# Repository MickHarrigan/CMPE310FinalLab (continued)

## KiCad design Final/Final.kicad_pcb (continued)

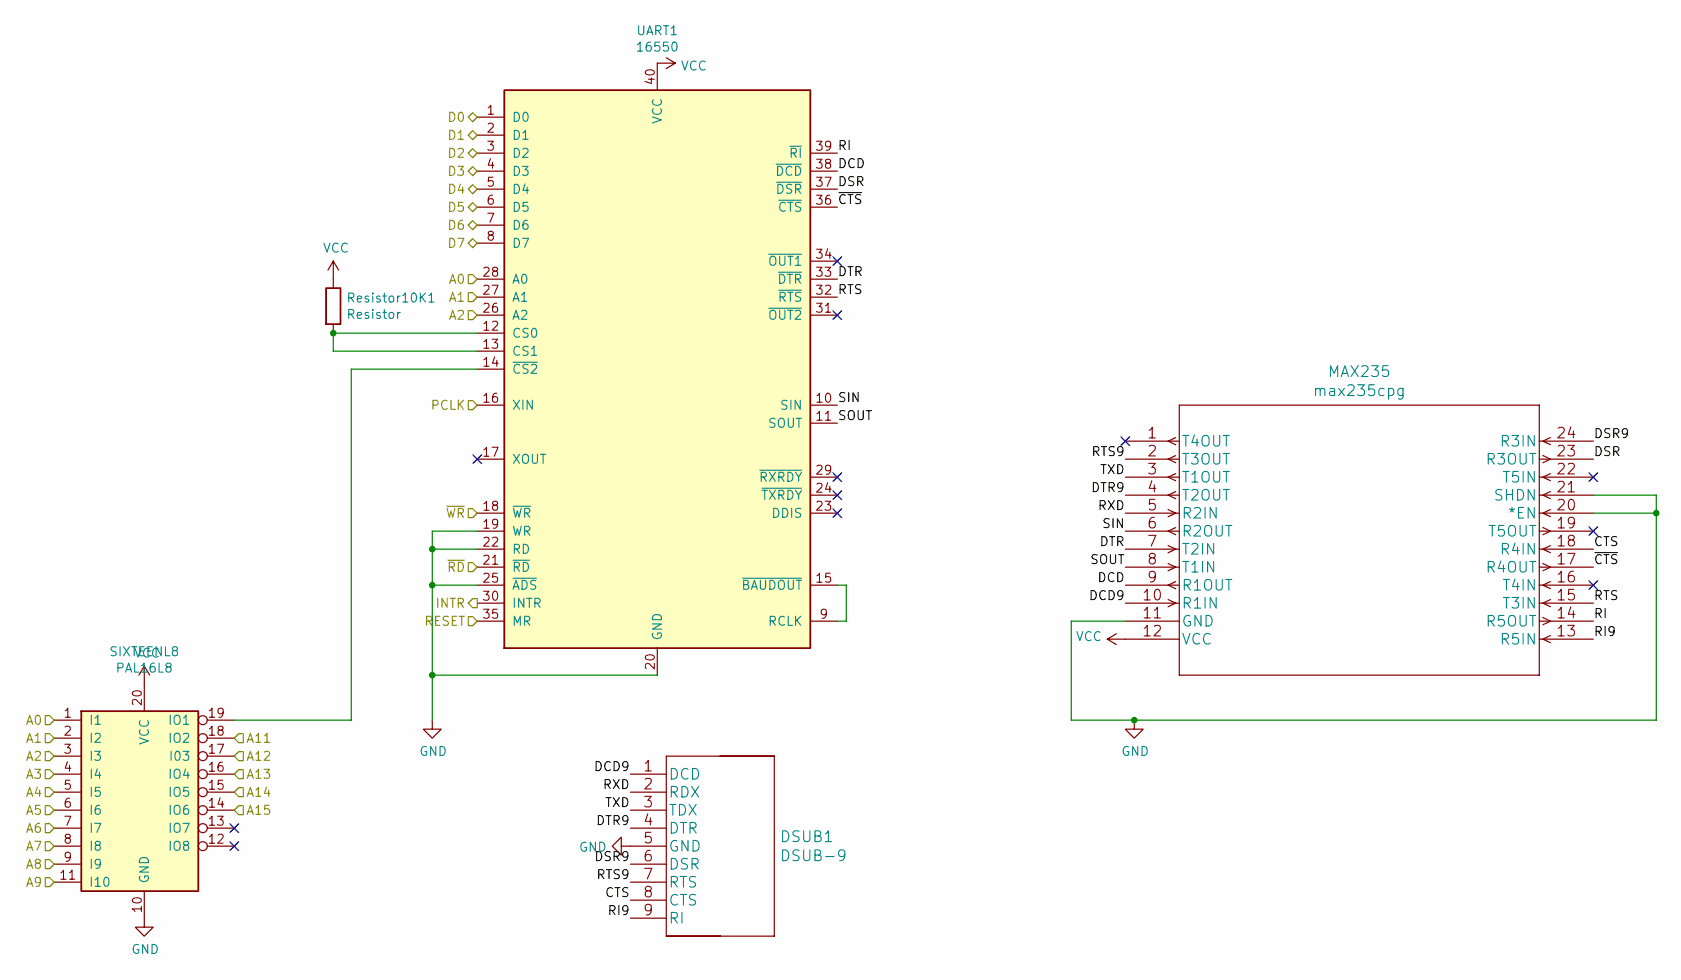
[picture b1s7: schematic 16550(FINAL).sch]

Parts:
DSUB1: DSUB-9
MAX235: max235cpg
Resistor10K1: Resistor
SIXTEENL8: PAL16L8
UART1: 16550; DIP-40_W15.24mm

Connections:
/16550/CTS: DSUB1.8 (CTS), MAX235.18 (R4IN)
/16550/DCD: MAX235.9 (R1OUT), UART1.38 (~DCD~)
/16550/DCD9: DSUB1.1 (DCD), MAX235.10 (R1IN)
/16550/DSR: MAX235.23 (R3OUT), UART1.37 (~DSR~)
/16550/DSR9: DSUB1.6 (DSR), MAX235.24 (R3IN)
/16550/DTR: MAX235.7 (T2IN), UART1.33 (~DTR~)
/16550/DTR9: DSUB1.4 (DTR), MAX235.4 (T2OUT)
/16550/RI: MAX235.14 (R5OUT), UART1.39 (~RI~)
/16550/RI9: DSUB1.9 (RI), MAX235.13 (R5IN)
/16550/RTS: MAX235.15 (T3IN), UART1.32 (~RTS~)
/16550/RTS9: DSUB1.7 (RTS), MAX235.2 (T3OUT)
/16550/RXD: DSUB1.2 (RDX), MAX235.5 (R2IN)
/16550/SIN: MAX235.6 (R2OUT), UART1.10 (SIN)
/16550/SOUT: MAX235.8 (T1IN), UART1.11 (SOUT)
/16550/TXD: DSUB1.3 (TDX), MAX235.3 (T1OUT)
/16550/~CTS: MAX235.17 (R4OUT), UART1.36 (~CTS~)
/16550_INTR: UART1.30 (INTR); also elsewhere on the board
/A0: SIXTEENL8.1 (I1), UART1.28 (A0); also elsewhere on the board
/A1: SIXTEENL8.2 (I2), UART1.27 (A1); also elsewhere on the board
/A2: SIXTEENL8.3 (I3), UART1.26 (A2); also elsewhere on the board
/A3: SIXTEENL8.4 (I4); also elsewhere on the board
/A4: SIXTEENL8.5 (I5); also elsewhere on the board
/A5: SIXTEENL8.6 (I6); also elsewhere on the board
/A6: SIXTEENL8.7 (I7); also elsewhere on the board
/A7: SIXTEENL8.8 (I8); also elsewhere on the board
/A8: SIXTEENL8.9 (I9); also elsewhere on the board
/A9: SIXTEENL8.11 (I10); also elsewhere on the board
/A11: SIXTEENL8.18 (IO2); also elsewhere on the board
/A12: SIXTEENL8.17 (I03); also elsewhere on the board
/A13: SIXTEENL8.16 (IO4); also elsewhere on the board
/A14: SIXTEENL8.15 (IO5); also elsewhere on the board
/A15: SIXTEENL8.14 (IO6); also elsewhere on the board
/D0: UART1.1 (D0); also elsewhere on the board
/D1: UART1.2 (D1); also elsewhere on the board
/D2: UART1.3 (D2); also elsewhere on the board
/D3: UART1.4 (D3); also elsewhere on the board
/D4: UART1.5 (D4); also elsewhere on the board
/D5: UART1.6 (D5); also elsewhere on the board
/D6: UART1.7 (D6); also elsewhere on the board
/D7: UART1.8 (D7); also elsewhere on the board
/PCLK: UART1.16 (XIN); also elsewhere on the board
/RESET: UART1.35 (MR); also elsewhere on the board
/~RD: UART1.21 (~RD~); also elsewhere on the board
/~WR: UART1.18 (~WR~); also elsewhere on the board
GND: DSUB1.5 (GND), MAX235.11 (GND), MAX235.20 (*EN), MAX235.21 (SHDN), SIXTEENL8.10 (GND), UART1.19 (WR), UART1.20 (GND), UART1.22 (RD), UART1.25 (~ADS~); also elsewhere on the board
unnamed: Resistor10K1.2, UART1.12 (CS0), UART1.13 (CS1)
unnamed: SIXTEENL8.19 (IO1), UART1.14 (~CS2~)
unnamed: UART1.9 (RCLK), UART1.15 (~BAUDOUT~)
VCC: MAX235.12 (VCC), Resistor10K1.1, SIXTEENL8.20 (VCC), UART1.40 (VCC); also elsewhere on the board

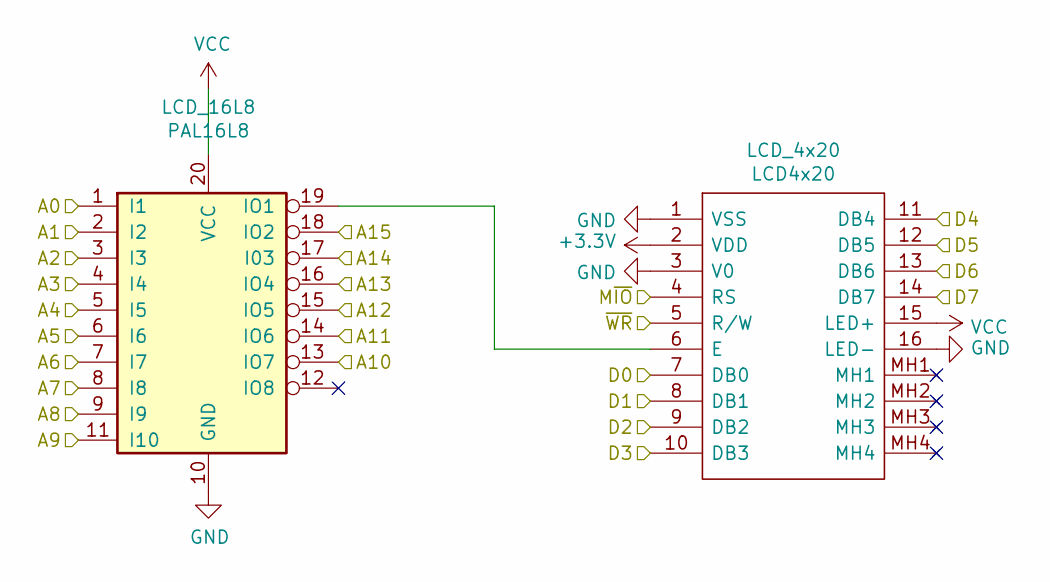
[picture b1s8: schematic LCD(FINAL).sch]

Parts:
LCD_4x20: LCD4x20; Mouser Part Number 763-0420AZFLYBW33V3
LCD_16L8: PAL16L8

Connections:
+3V3: LCD_4x20.2 (VDD)
/A0: LCD_16L8.1 (I1); also elsewhere on the board
/A1: LCD_16L8.2 (I2); also elsewhere on the board
/A2: LCD_16L8.3 (I3); also elsewhere on the board
/A3: LCD_16L8.4 (I4); also elsewhere on the board
/A4: LCD_16L8.5 (I5); also elsewhere on the board
/A5: LCD_16L8.6 (I6); also elsewhere on the board
/A6: LCD_16L8.7 (I7); also elsewhere on the board
/A7: LCD_16L8.8 (I8); also elsewhere on the board
/A8: LCD_16L8.9 (I9); also elsewhere on the board
/A9: LCD_16L8.11 (I10); also elsewhere on the board
/A10: LCD_16L8.13 (IO7); also elsewhere on the board
/A11: LCD_16L8.14 (IO6); also elsewhere on the board
/A12: LCD_16L8.15 (IO5); also elsewhere on the board
/A13: LCD_16L8.16 (IO4); also elsewhere on the board
/A14: LCD_16L8.17 (I03); also elsewhere on the board
/A15: LCD_16L8.18 (IO2); also elsewhere on the board
/D0: LCD_4x20.7 (DB0); also elsewhere on the board
/D1: LCD_4x20.8 (DB1); also elsewhere on the board
/D2: LCD_4x20.9 (DB2); also elsewhere on the board
/D3: LCD_4x20.10 (DB3); also elsewhere on the board
/D4: LCD_4x20.11 (DB4); also elsewhere on the board
/D5: LCD_4x20.12 (DB5); also elsewhere on the board
/D6: LCD_4x20.13 (DB6); also elsewhere on the board
/D7: LCD_4x20.14 (DB7); also elsewhere on the board
/M~IO: LCD_4x20.4 (RS); also elsewhere on the board
/~WR: LCD_4x20.5 (R/W); also elsewhere on the board
GND: LCD_4x20.1 (VSS), LCD_4x20.3 (V0), LCD_4x20.16 (LED-), LCD_16L8.10 (GND); also elsewhere on the board
unnamed: LCD_4x20.6 (E), LCD_16L8.19 (IO1)
VCC: LCD_4x20.15 (LED+), LCD_16L8.20 (VCC); also elsewhere on the board

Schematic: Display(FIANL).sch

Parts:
D2, D3, D4, D5, D6, D7, D8, D9: LED
Display1, Display2, Display3: 74LS374
Display_Decode1, Display_Decode2: PAL16L8
R4, R5: R
R6, R7, R8, R9, R10, R11, R12, R13: 330
Seven_Seg1, Seven_Seg2: MAN71A

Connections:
/A0: Display_Decode2.11 (I10); also elsewhere on the board
/A1: Display_Decode2.9 (I9); also elsewhere on the board
/A2: Display_Decode2.8 (I8); also elsewhere on the board
/A3: Display_Decode2.7 (I7); also elsewhere on the board
/A4: Display_Decode2.6 (I6); also elsewhere on the board
/A5: Display_Decode2.5 (I5); also elsewhere on the board
/A6: Display_Decode2.4 (I4); also elsewhere on the board
/A7: Display_Decode2.3 (I3); also elsewhere on the board
/A8: Display_Decode1.11 (I10); also elsewhere on the board
/A9: Display_Decode1.9 (I9); also elsewhere on the board
/A10: Display_Decode1.8 (I8); also elsewhere on the board
/A11: Display_Decode1.7 (I7); also elsewhere on the board
/A12: Display_Decode1.6 (I6); also elsewhere on the board
/A13: Display_Decode1.5 (I5); also elsewhere on the board
/A14: Display_Decode1.4 (I4); also elsewhere on the board
/A15: Display_Decode1.3 (I3); also elsewhere on the board
/D0: Display2.18 (D7), Display3.18 (D7); also elsewhere on the board
/D1: Display2.17 (D6), Display3.17 (D6); also elsewhere on the board
/D2: Display2.14 (D5), Display3.14 (D5); also elsewhere on the board
/D3: Display2.13 (D4), Display3.13 (D4); also elsewhere on the board
/D4: Display2.8 (D3), Display3.8 (D3); also elsewhere on the board
/D5: Display2.7 (D2), Display3.7 (D2); also elsewhere on the board
/D6: Display2.4 (D1), Display3.4 (D1); also elsewhere on the board
/D7: Display2.3 (D0), Display3.3 (D0); also elsewhere on the board
/D8: Display1.18 (D7); also elsewhere on the board
/D9: Display1.17 (D6); also elsewhere on the board
/D10: Display1.14 (D5); also elsewhere on the board
/D11: Display1.13 (D4); also elsewhere on the board
/D12: Display1.8 (D3); also elsewhere on the board
/D13: Display1.7 (D2); also elsewhere on the board
/D14: Display1.4 (D1); also elsewhere on the board
/D15: Display1.3 (D0); also elsewhere on the board
/~WR: Display_Decode1.2 (I2), Display_Decode2.2 (I2); also elsewhere on the board
GND: Display1.1 (OE), Display1.10 (GND), Display2.1 (OE), Display2.10 (GND), Display3.1 (OE), Display3.10 (GND), Display_Decode1.10 (GND), Display_Decode2.10 (GND); also elsewhere on the board
unnamed: D2.1 (K), Display3.12 (O4)
unnamed: D2.2 (A), R6.2
unnamed: D3.1 (K), Display3.2 (O0)
unnamed: D3.2 (A), R7.2
unnamed: D4.1 (K), Display3.6 (O2)
unnamed: D4.2 (A), R8.2
unnamed: D5.1 (K), Display3.16 (O6)
unnamed: D5.2 (A), R9.2
unnamed: D6.1 (K), Display3.9 (O3)
unnamed: D6.2 (A), R10.2
unnamed: D7.1 (K), Display3.15 (O5)
unnamed: D7.2 (A), R11.2
unnamed: D8.1 (K), Display3.19 (O7)
unnamed: D8.2 (A), R12.2
unnamed: D9.1 (K), Display3.5 (O1)
unnamed: D9.2 (A), R13.2
unnamed: Display1.2 (O0), Seven_Seg1.1 (A)
unnamed: Display1.5 (O1), Seven_Seg1.13 (B)
unnamed: Display1.6 (O2), Seven_Seg1.10 (C)
unnamed: Display1.9 (O3), Seven_Seg1.8 (D)
unnamed: Display1.11 (Cp), Display_Decode1.19 (IO1)
unnamed: Display1.12 (O4), Seven_Seg1.7 (E)
unnamed: Display1.15 (O5), Seven_Seg1.2 (F)
unnamed: Display1.16 (O6), Seven_Seg1.11 (G)
unnamed: Display1.19 (O7), Seven_Seg1.9 (D.P.)
unnamed: Display2.2 (O0), Seven_Seg2.1 (A)
unnamed: Display2.5 (O1), Seven_Seg2.13 (B)
unnamed: Display2.6 (O2), Seven_Seg2.10 (C)
unnamed: Display2.9 (O3), Seven_Seg2.8 (D)
unnamed: Display2.11 (Cp), Display_Decode2.19 (IO1)
unnamed: Display2.12 (O4), Seven_Seg2.7 (E)
unnamed: Display2.15 (O5), Seven_Seg2.2 (F)
unnamed: Display2.16 (O6), Seven_Seg2.11 (G)
unnamed: Display2.19 (O7), Seven_Seg2.9 (D.P.)
unnamed: Display3.11 (Cp), Display_Decode2.18 (IO2)
unnamed: R4.2, Seven_Seg1.14 (CA)
unnamed: R5.2, Seven_Seg2.14 (CA)
VCC: Display1.20 (VCC), Display2.20 (VCC), Display3.20 (VCC), Display_Decode1.20 (VCC), Display_Decode2.20 (VCC), R4.1, R5.1, R6.1, R7.1, R8.1, R9.1, R10.1, R11.1, R12.1, R13.1; also elsewhere on the board

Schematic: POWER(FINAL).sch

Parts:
C3, C4, C5, C6, C7, C8, C9, C10, C11, C12, C13, C14, C15, C16, C17, C18, C19, C20, C21, C22, C23, C24, C25, C26, C27, C28: CP1_Small
Power_1: Conn_01x02_Female

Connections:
unnamed: C3.1, C4.1, C5.1, C6.1, C7.1, C8.1, C9.1, C10.1, C11.1, C12.1, C13.1, C14.1, C15.1, C16.1, C17.1, C18.1, C19.1, C20.1, C21.1, C22.1, C23.1, C24.1, C25.1, C26.1, C27.1, C28.1, Power_1.1
VCC: C3.2, C4.2, C5.2, C6.2, C7.2, C8.2, C9.2, C10.2, C11.2, C12.2, C13.2, C14.2, C15.2, C16.2, C17.2, C18.2, C19.2, C20.2, C21.2, C22.2, C23.2, C24.2, C25.2, C26.2, C27.2, C28.2, Power_1.2; also elsewhere on the board

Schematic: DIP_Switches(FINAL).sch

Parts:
DIP_16LA1: PAL16L8
DIP_LS244: 74LS244
DIP_Switches1: SW_DIP_x08
R14, R15, R16, R17, R18, R19, R20, R21: R_Small_US

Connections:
/A0: DIP_16LA1.1 (I1); also elsewhere on the board
/A1: DIP_16LA1.2 (I2); also elsewhere on the board
/A2: DIP_16LA1.3 (I3); also elsewhere on the board
/A3: DIP_16LA1.4 (I4); also elsewhere on the board
/A4: DIP_16LA1.5 (I5); also elsewhere on the board
/A5: DIP_16LA1.6 (I6); also elsewhere on the board
/A6: DIP_16LA1.7 (I7); also elsewhere on the board
/A7: DIP_16LA1.8 (I8); also elsewhere on the board
/A8: DIP_16LA1.9 (I9); also elsewhere on the board
/A9: DIP_16LA1.11 (I10); also elsewhere on the board
/A11: DIP_16LA1.18 (IO2); also elsewhere on the board
/A12: DIP_16LA1.17 (I03); also elsewhere on the board
/A13: DIP_16LA1.16 (IO4); also elsewhere on the board
/A14: DIP_16LA1.15 (IO5); also elsewhere on the board
/A15: DIP_16LA1.14 (IO6); also elsewhere on the board
/D0: DIP_LS244.18 (O0a); also elsewhere on the board
/D1: DIP_LS244.16 (O1a); also elsewhere on the board
/D2: DIP_LS244.14 (O2a); also elsewhere on the board
/D3: DIP_LS244.12 (O3a); also elsewhere on the board
/D4: DIP_LS244.9 (O0b); also elsewhere on the board
/D5: DIP_LS244.7 (O1b); also elsewhere on the board
/D6: DIP_LS244.5 (O2b); also elsewhere on the board
/D7: DIP_LS244.3 (O3b); also elsewhere on the board
GND: DIP_16LA1.10 (GND), DIP_LS244.1 (OEa), DIP_LS244.10 (GND), DIP_Switches1.9, DIP_Switches1.10, DIP_Switches1.11, DIP_Switches1.12, DIP_Switches1.13, DIP_Switches1.14, DIP_Switches1.15, DIP_Switches1.16, R14.2, R15.2, R16.2, R17.2, R18.2, R19.2, R20.2, R21.2; also elsewhere on the board
unnamed: DIP_16LA1.19 (IO1), DIP_LS244.19 (OEb)
unnamed: DIP_LS244.2 (I0a), DIP_Switches1.8, R21.1
unnamed: DIP_LS244.4 (I1a), DIP_Switches1.7, R20.1
unnamed: DIP_LS244.6 (I2a), DIP_Switches1.6, R19.1
unnamed: DIP_LS244.8 (I3a), DIP_Switches1.5, R18.1
unnamed: DIP_LS244.11 (I0b), DIP_Switches1.4, R17.1
unnamed: DIP_LS244.13 (I1b), DIP_Switches1.3, R16.1
unnamed: DIP_LS244.15 (I2b), DIP_Switches1.2, R15.1
unnamed: DIP_LS244.17 (I3b), DIP_Switches1.1, R14.1
VCC: DIP_16LA1.20 (VCC), DIP_LS244.20 (VCC); also elsewhere on the board

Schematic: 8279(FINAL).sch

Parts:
8279Keyboard1: pkd8279
KeyboardSelector1: PAL16L8
SW4, SW5, SW6, SW7, SW8, SW9, SW10, SW11, SW12, SW13, SW14, SW15, SW16, SW17, SW18, SW19, SW20, SW21, SW22, SW23, SW24, SW25: SW_Push

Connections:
+5V: 8279Keyboard1.40 (VCC), KeyboardSelector1.20 (VCC); also elsewhere on the board
/8279/CNTRL: 8279Keyboard1.37 (CNTL/STB), SW25.1
/8279/CS: 8279Keyboard1.22 (~CS), KeyboardSelector1.19 (IO1)
/8279/Col0: 8279Keyboard1.38 (RL0), SW4.2, SW5.2, SW6.2, SW7.2
/8279/Col1: 8279Keyboard1.39 (RL1), SW8.2, SW9.2, SW10.2, SW11.2
/8279/Col2: 8279Keyboard1.1 (RL2), SW12.2, SW13.2, SW14.2, SW15.2
/8279/Col3: 8279Keyboard1.2 (RL3), SW16.2, SW17.2, SW18.2, SW19.2
/8279/Col4: 8279Keyboard1.5 (RL4), SW20.2, SW21.2, SW22.2, SW23.2
/8279/Row0: 8279Keyboard1.32 (SL0), SW4.1, SW8.1, SW12.1, SW16.1, SW20.1
/8279/Row1: 8279Keyboard1.33 (SL1), SW5.1, SW9.1, SW13.1, SW17.1, SW21.1
/8279/Row2: 8279Keyboard1.34 (SL2), SW6.1, SW10.1, SW14.1, SW18.1, SW22.1
/8279/Row3: 8279Keyboard1.35 (SL3), SW7.1, SW11.1, SW15.1, SW19.1, SW23.1
/8279/Shift: 8279Keyboard1.36 (SHIFT), SW24.1
/A1: 8279Keyboard1.21 (A0); also elsewhere on the board
/A2: KeyboardSelector1.1 (I1); also elsewhere on the board
/A3: KeyboardSelector1.2 (I2); also elsewhere on the board
/A4: KeyboardSelector1.3 (I3); also elsewhere on the board
/A5: KeyboardSelector1.4 (I4); also elsewhere on the board
/A6: KeyboardSelector1.5 (I5); also elsewhere on the board
/A7: KeyboardSelector1.6 (I6); also elsewhere on the board
/A8: KeyboardSelector1.7 (I7); also elsewhere on the board
/A9: KeyboardSelector1.8 (I8); also elsewhere on the board
/A10: KeyboardSelector1.9 (I9); also elsewhere on the board
/A11: KeyboardSelector1.11 (I10); also elsewhere on the board
/A12: KeyboardSelector1.14 (IO6); also elsewhere on the board
/A13: KeyboardSelector1.15 (IO5); also elsewhere on the board
/A14: KeyboardSelector1.16 (IO4); also elsewhere on the board
/A15: KeyboardSelector1.17 (I03); also elsewhere on the board
/D0: 8279Keyboard1.12 (DB0); also elsewhere on the board
/D1: 8279Keyboard1.13 (DB1); also elsewhere on the board
/D2: 8279Keyboard1.14 (DB2); also elsewhere on the board
/D3: 8279Keyboard1.15 (DB3); also elsewhere on the board
/D4: 8279Keyboard1.16 (DB4); also elsewhere on the board
/D5: 8279Keyboard1.17 (DB5); also elsewhere on the board
/D6: 8279Keyboard1.18 (DB6); also elsewhere on the board
/D7: 8279Keyboard1.19 (DB7); also elsewhere on the board
/IRQ: 8279Keyboard1.4 (IRQ); also elsewhere on the board
/M~IO: KeyboardSelector1.13 (IO7); also elsewhere on the board
/PCLK: 8279Keyboard1.3 (CLK); also elsewhere on the board
/RESET: 8279Keyboard1.9 (RESET); also elsewhere on the board
/~RD: 8279Keyboard1.10 (~RD); also elsewhere on the board
/~WR: 8279Keyboard1.11 (~WR); also elsewhere on the board
GND: 8279Keyboard1.20 (VSS), KeyboardSelector1.10 (GND), SW24.2, SW25.2; also elsewhere on the board

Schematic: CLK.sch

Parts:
C2: 10uF
R2: 10k
SW2: SW_DPST_x2
U8: 8284; DIP-18_W7.62mm
Y1: Crystal

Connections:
unnamed: C2.1, R2.2, SW2.1 (A), U8.11 (~RES~)
unnamed: C2.2, SW2.2 (B), U8.1 (CSYNC), U8.13 (F/~C~)
unnamed: R2.1, U8.18 (VCC)
unnamed: U8.16 (X2), Y1.1
unnamed: U8.17 (X1), Y1.2

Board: 2 copper layers, 146 parts (0 on the bottom side), 258 nets, no tracks yet.

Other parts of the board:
CLK1: 8284; DIP-18_W7.62mm
CLK_Capacitor1: 10uF; CP_Axial_L10.0mm_D4.5mm_P15.00mm_Horizontal
CLK_Resistor1: 10k; R_Axial_DIN0204_L3.6mm_D1.6mm_P1.90mm_Vertical
CLK_Switch1: SW_DPST_x2; Push_E-Switch_KS01Q01
CMOS1: 28F010; DIP-32_W7.62mm
CRYSTAL1: Crystal; Crystal_AT310_D3.0mm_L10.0mm_Vertical
U41: 28F010; DIP-32_W7.62mm

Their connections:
+12V: CMOS1.1, U41.1
/8086/READY: CLK1.5; also elsewhere on the board
/A0: CMOS1.12, U41.12; also elsewhere on the board
/A1: CMOS1.11, U41.11; also elsewhere on the board
/A2: CMOS1.10, U41.10; also elsewhere on the board
/A3: CMOS1.9, U41.9; also elsewhere on the board
/A4: CMOS1.8, U41.8; also elsewhere on the board
/A5: CMOS1.7, U41.7; also elsewhere on the board
/A6: CMOS1.6, U41.6; also elsewhere on the board
/A7: CMOS1.5, U41.5; also elsewhere on the board
/A8: CMOS1.27, U41.27; also elsewhere on the board
/A9: CMOS1.26, U41.26; also elsewhere on the board
/A10: CMOS1.23, U41.23; also elsewhere on the board
/A11: CMOS1.25, U41.25; also elsewhere on the board
/A12: CMOS1.4, U41.4; also elsewhere on the board
/A13: CMOS1.28, U41.28; also elsewhere on the board
/A14: CMOS1.29, U41.29; also elsewhere on the board
/A15: CMOS1.3, U41.3; also elsewhere on the board
/A16: CMOS1.2, U41.2; also elsewhere on the board
/CLK: CLK1.8; also elsewhere on the board
/CMOS Flash/CMOSHierarchal1/CS: CMOS1.22; also elsewhere on the board
/CMOS Flash/CMOSHierarchal/CS: U41.22; also elsewhere on the board
/D0: CMOS1.13, U41.13; also elsewhere on the board
/D1: CMOS1.14, U41.14; also elsewhere on the board
/D2: CMOS1.15, U41.15; also elsewhere on the board
/D3: CMOS1.17, U41.17; also elsewhere on the board
/D4: CMOS1.18, U41.18; also elsewhere on the board
/D5: CMOS1.19, U41.19; also elsewhere on the board
/D6: CMOS1.20, U41.20; also elsewhere on the board
/D7: CMOS1.21, U41.21; also elsewhere on the board
/PCLK: CLK1.2; also elsewhere on the board
/RESET: CLK1.10; also elsewhere on the board
/~RD: CMOS1.24, U41.24; also elsewhere on the board
/~WR: CMOS1.31, U41.31; also elsewhere on the board
GND: CLK1.1, CLK1.9, CLK1.13, CLK_Capacitor1.2, CLK_Switch1.2, CMOS1.16, U41.16; also elsewhere on the board
unnamed: CLK1.11, CLK_Capacitor1.1, CLK_Resistor1.2, CLK_Switch1.1
unnamed: CLK1.16, CRYSTAL1.1
unnamed: CLK1.17, CRYSTAL1.2
VCC: CLK1.18, CLK_Resistor1.1, CMOS1.32, U41.32; also elsewhere on the board

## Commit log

2021-04-13 Ignore, Testing Git
2021-04-13 parts file
2021-04-14 8086 chip (still needs clock inputs)
2021-04-14 Fixed some spelling mistakes
2021-04-14 Fixed Labels
2021-04-14 integrated clock
2021-04-14 Some minor changes
2021-04-14 Add files via upload
    added ready pin to clk
2021-04-14 Add files via upload
    Added PCLK as a hierarchical label to CLK
2021-04-14 Add files via upload
    Updated Hierarchical labels
2021-04-15 power block i think
2021-04-15 8259 Project page
    .sch file for the layout of the 8259
2021-04-15 8279 Schematic
    Hopefully this connects to everything else
2021-04-15 7 segment Display
2021-04-20 minor changes
2021-04-24 8254
2021-04-28 DIP Switches
2021-04-29 updated bus labels and pins
2021-04-29 updated bus labels
2021-04-29 updated counters
2021-04-29 done I hope...
2021-04-29 Final Compilation
2021-04-29 For final compilation
2021-05-03 New stuff
2021-05-03 updated pins instead of busses
2021-05-03 added A2
2021-05-03 3 chips
2021-05-03 For Commenting
2021-05-03 Stuffs
2021-05-04 annotations
2021-05-04 Final?
2021-05-04 Final..I Hope
2021-05-04 added .net
2021-05-04 netlist for Final
2021-05-04 Hopefully the board is here
2021-05-06 this shizz
2021-05-06 Added correct footprints
2021-05-09 Added some final touches
2021-05-09 Add files via upload
    Project Description
